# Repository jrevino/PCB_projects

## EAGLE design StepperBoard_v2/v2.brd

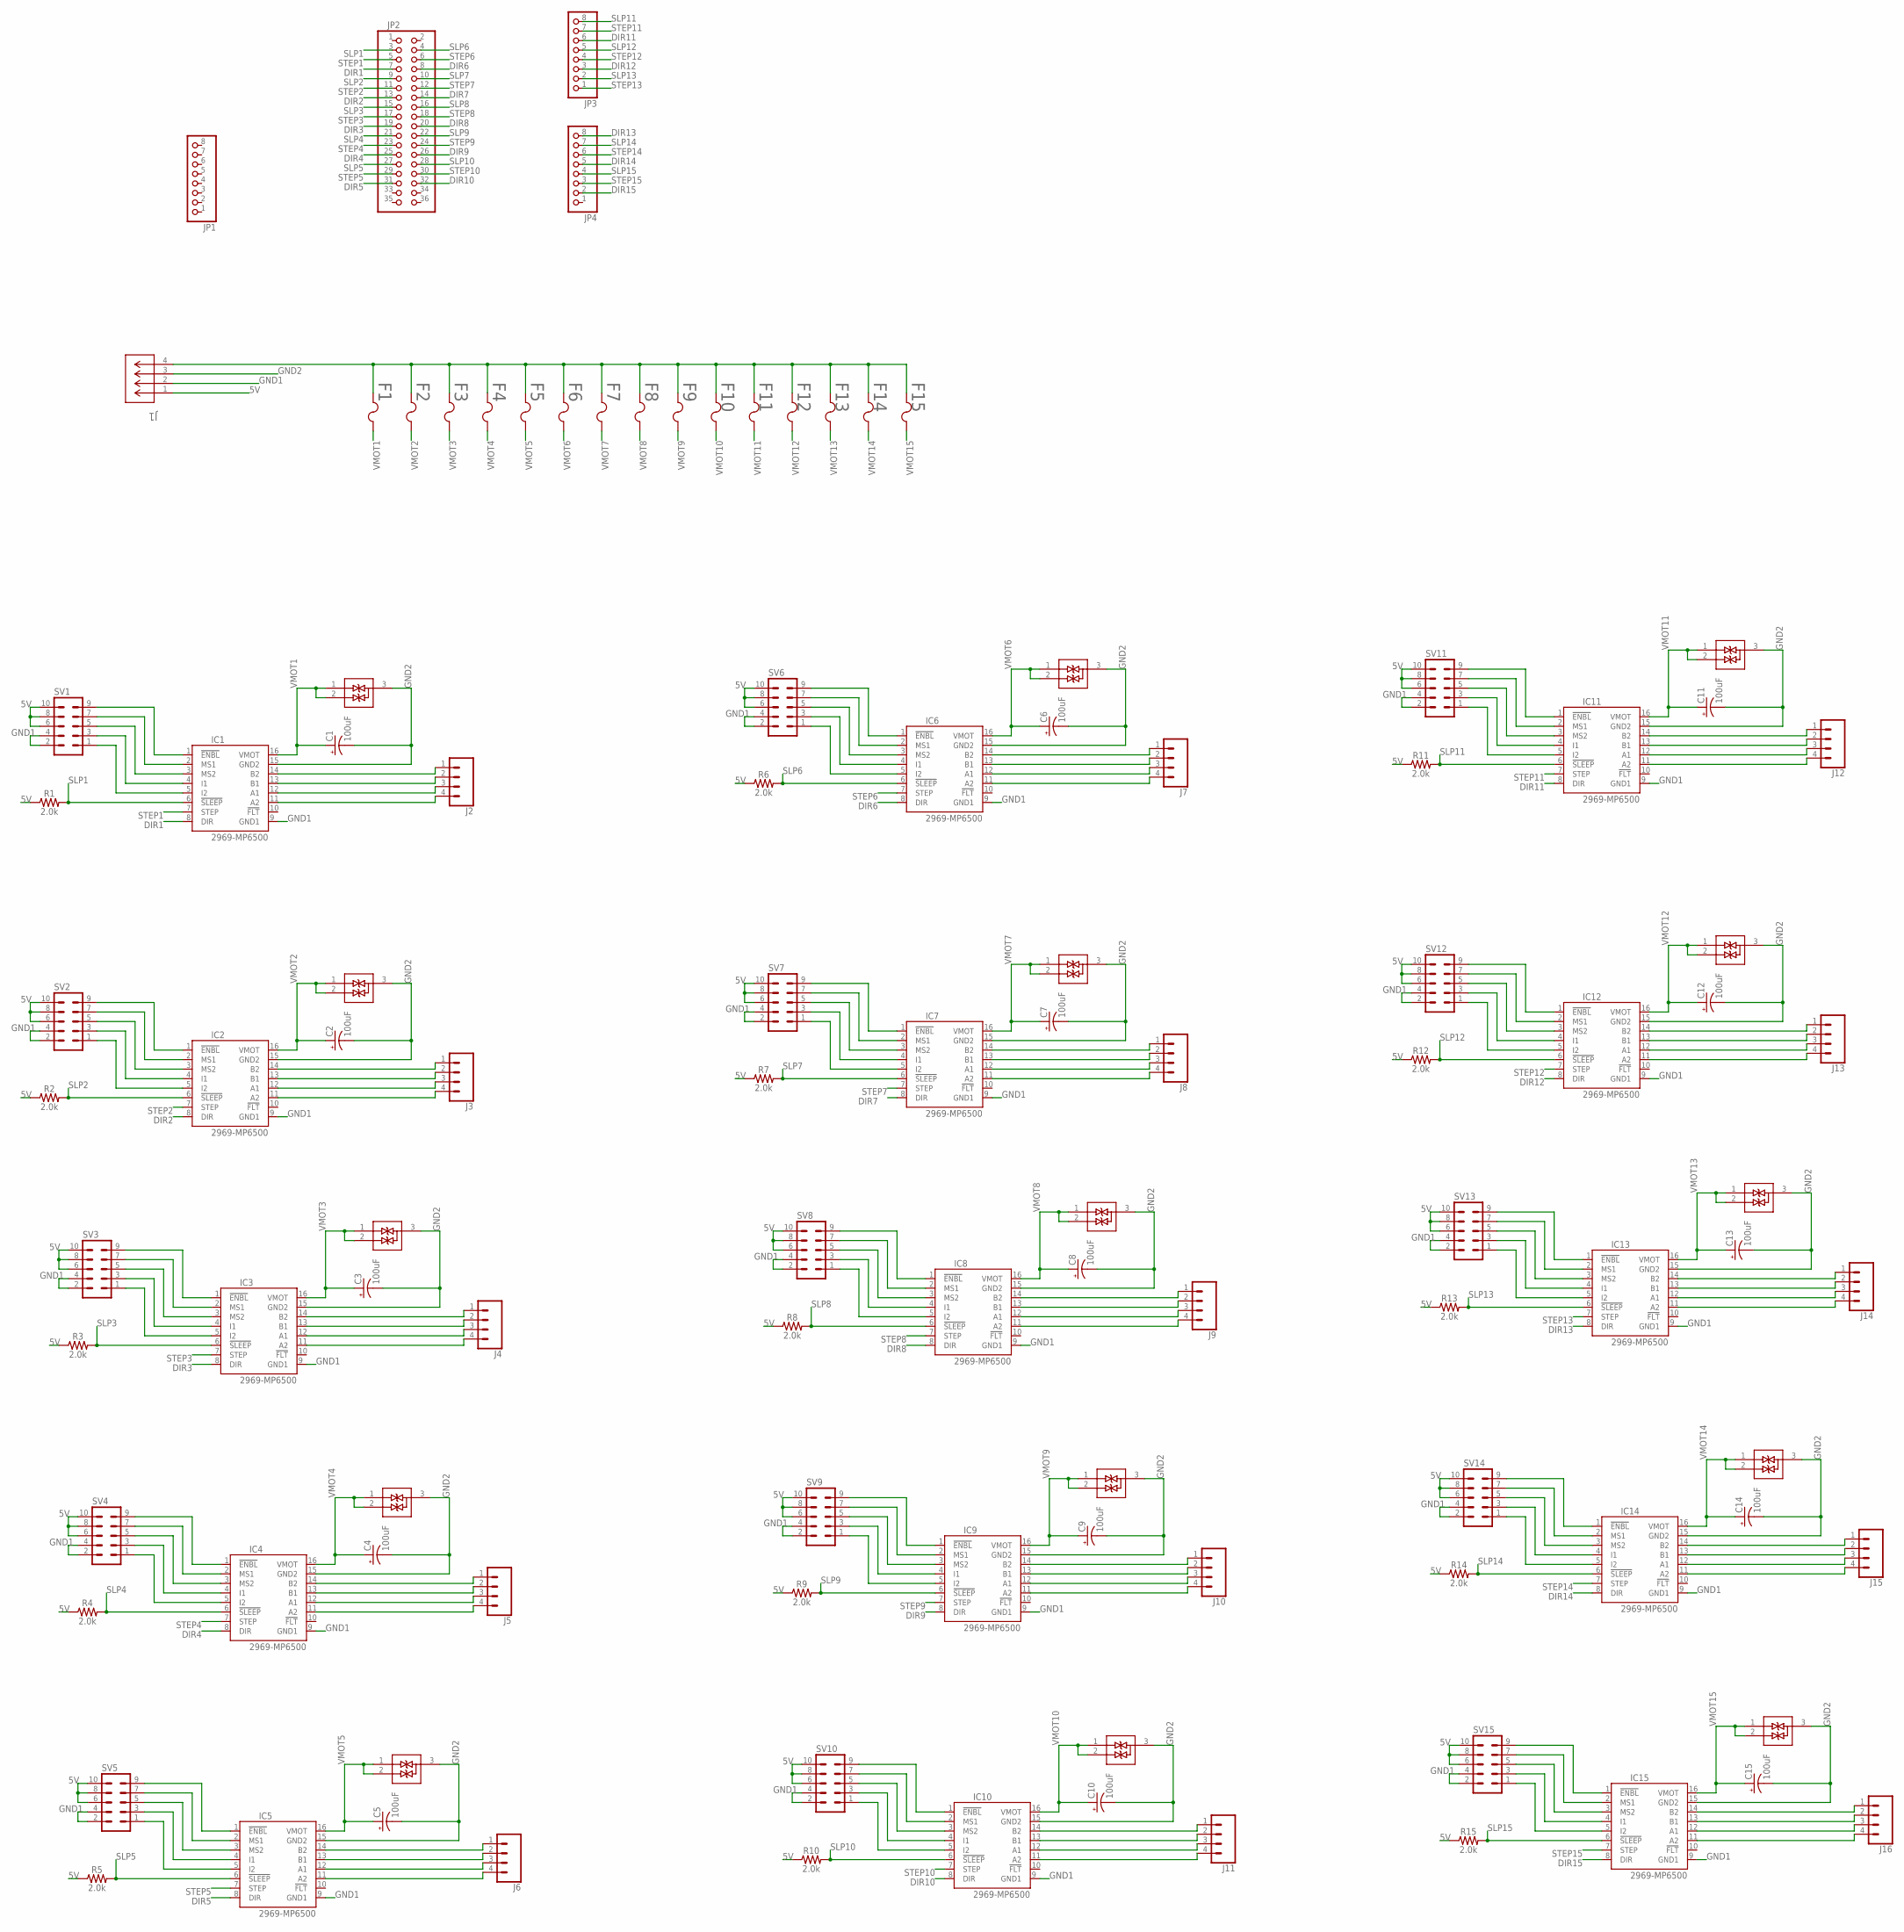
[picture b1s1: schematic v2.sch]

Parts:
C1, C2, C3, C4, C5, C6, C7, C8, C9, C10, C11, C12, C13, C14, C15: 100uF; 8X10.5
CR1, CR2, CR3, CR4, CR5, CR6, CR7, CR8, CR9, CR10, CR11, CR12, CR13, CR14, CR15: PESD2CAN24DBZRQ1; SOT-23_DBZ_TEX
F1, F2, F3, F4, F5, F6, F7, F8, F9, F10, F11, F12, F13, F14, F15: 0154003.DR; 0154SERIES_LTF
IC1, IC2, IC3, IC4, IC5, IC6, IC7, IC8, IC9, IC10, IC11, IC12, IC13, IC14, IC15: 2969-MP6500; MP6500
J1: 1888700; CONN_1888700_PXC
J2, J3, J4, J5, J6, J7, J8, J9, J10, J11, J12, J13, J14, J15, J16: CONN_04POLAR_LOCK; MOLEX-1X4_LOCK
JP1, JP3, JP4: PINHD-1X8; 1X08
JP2: PINHD-2X18; 2X18
R1, R2, R3, R4, R5, R6, R7, R8, R9, R10, R11, R12, R13, R14, R15: 2.0k; 0603
SV1, SV2, SV3, SV4, SV5, SV6, SV7, SV8, SV9, SV10, SV11, SV12, SV13, SV14, SV15: MA05-2

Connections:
5V: J1.1, R1.1, R2.1, R3.1, R4.1, R5.1, R6.1, R7.1, R8.1, R9.1, R10.1, R11.1, R12.1, R13.1, R14.1, R15.1, SV1.6, SV1.8, SV1.10, SV2.6, SV2.8, SV2.10, SV3.6, SV3.8, SV3.10, SV4.6, SV4.8, SV4.10, SV5.6, SV5.8, SV5.10, SV6.6, SV6.8, SV6.10, SV7.6, SV7.8, SV7.10, SV8.6, SV8.8, SV8.10, SV9.6, SV9.8, SV9.10, SV10.6, SV10.8, SV10.10, SV11.6, SV11.8, SV11.10, SV12.6, SV12.8, SV12.10, SV13.6, SV13.8, SV13.10, SV14.6, SV14.8, SV14.10, SV15.6, SV15.8, SV15.10
DIR1: IC1.8 (DIR), JP2.7
DIR2: IC2.8 (DIR), JP2.13
DIR3: IC3.8 (DIR), JP2.19
DIR4: IC4.8 (DIR), JP2.25
DIR5: IC5.8 (DIR), JP2.31
DIR6: IC6.8 (DIR), JP2.8
DIR7: IC7.8 (DIR), JP2.14
DIR8: IC8.8 (DIR), JP2.20
DIR9: IC9.8 (DIR), JP2.26
DIR10: IC10.8 (DIR), JP2.32
DIR11: IC11.8 (DIR), JP3.6
DIR12: IC12.8 (DIR), JP3.3
DIR13: IC13.8 (DIR), JP4.8
DIR14: IC14.8 (DIR), JP4.5
DIR15: IC15.8 (DIR), JP4.2
GND1: IC1.9 (GND1), IC2.9 (GND1), IC3.9 (GND1), IC4.9 (GND1), IC5.9 (GND1), IC6.9 (GND1), IC7.9 (GND1), IC8.9 (GND1), IC9.9 (GND1), IC10.9 (GND1), IC11.9 (GND1), IC12.9 (GND1), IC13.9 (GND1), IC14.9 (GND1), IC15.9 (GND1), J1.2, SV1.2, SV1.4, SV2.2, SV2.4, SV3.2, SV3.4, SV4.2, SV4.4, SV5.2, SV5.4, SV6.2, SV6.4, SV7.2, SV7.4, SV8.2, SV8.4, SV9.2, SV9.4, SV10.2, SV10.4, SV11.2, SV11.4, SV12.2, SV12.4, SV13.2, SV13.4, SV14.2, SV14.4, SV15.2, SV15.4
GND2: C1.-, C2.-, C3.-, C4.-, C5.-, C6.-, C7.-, C8.-, C9.-, C10.-, C11.-, C12.-, C13.-, C14.-, C15.-, CR1.3, CR2.3, CR3.3, CR4.3, CR5.3, CR6.3, CR7.3, CR8.3, CR9.3, CR10.3, CR11.3, CR12.3, CR13.3, CR14.3, CR15.3, IC1.15 (GND2), IC2.15 (GND2), IC3.15 (GND2), IC4.15 (GND2), IC5.15 (GND2), IC6.15 (GND2), IC7.15 (GND2), IC8.15 (GND2), IC9.15 (GND2), IC10.15 (GND2), IC11.15 (GND2), IC12.15 (GND2), IC13.15 (GND2), IC14.15 (GND2), IC15.15 (GND2), J1.3
unnamed: IC1.14 (B2), J2.1
unnamed: IC1.13 (B1), J2.2
unnamed: IC1.12 (A1), J2.3
unnamed: IC1.11 (A2), J2.4
unnamed: IC1.5 (I2), SV1.1
unnamed: IC1.4 (I1), SV1.3
unnamed: IC1.3 (MS2), SV1.5
unnamed: IC1.2 (MS1), SV1.7
unnamed: IC1.1 (!ENBL), SV1.9
unnamed: F1.1, F2.1, F3.1, F4.1, F5.1, F6.1, F7.1, F8.1, F9.1, F10.1, F11.1, F12.1, F13.1, F14.1, F15.1, J1.4
unnamed: IC2.5 (I2), SV2.1
unnamed: IC3.5 (I2), SV3.1
unnamed: IC3.4 (I1), SV3.3
unnamed: IC3.3 (MS2), SV3.5
unnamed: IC3.2 (MS1), SV3.7
unnamed: IC3.1 (!ENBL), SV3.9
unnamed: IC3.14 (B2), J4.1
unnamed: IC3.13 (B1), J4.2
unnamed: IC3.12 (A1), J4.3
unnamed: IC3.11 (A2), J4.4
unnamed: IC4.5 (I2), SV4.1
unnamed: IC4.4 (I1), SV4.3
unnamed: IC4.3 (MS2), SV4.5
unnamed: IC4.2 (MS1), SV4.7
unnamed: IC4.1 (!ENBL), SV4.9
unnamed: IC2.4 (I1), SV2.3
unnamed: IC2.3 (MS2), SV2.5
unnamed: IC2.2 (MS1), SV2.7
unnamed: IC2.1 (!ENBL), SV2.9
unnamed: IC2.14 (B2), J3.1
unnamed: IC2.13 (B1), J3.2
unnamed: IC2.12 (A1), J3.3
unnamed: IC2.11 (A2), J3.4
unnamed: IC4.14 (B2), J5.1
unnamed: IC4.13 (B1), J5.2
unnamed: IC4.12 (A1), J5.3
unnamed: IC4.11 (A2), J5.4
unnamed: IC6.5 (I2), SV6.1
unnamed: IC6.4 (I1), SV6.3
unnamed: IC6.3 (MS2), SV6.5
unnamed: IC6.2 (MS1), SV6.7
unnamed: IC6.1 (!ENBL), SV6.9
unnamed: IC6.14 (B2), J7.1
unnamed: IC6.13 (B1), J7.2
unnamed: IC6.12 (A1), J7.3
unnamed: IC6.11 (A2), J7.4
unnamed: IC5.5 (I2), SV5.1
unnamed: IC5.4 (I1), SV5.3
unnamed: IC5.3 (MS2), SV5.5
unnamed: IC5.2 (MS1), SV5.7
unnamed: IC5.1 (!ENBL), SV5.9
unnamed: IC5.14 (B2), J6.1
unnamed: IC5.13 (B1), J6.2
unnamed: IC5.12 (A1), J6.3
unnamed: IC5.11 (A2), J6.4
unnamed: IC7.5 (I2), SV7.1
unnamed: IC7.4 (I1), SV7.3
unnamed: IC7.3 (MS2), SV7.5
unnamed: IC7.2 (MS1), SV7.7
unnamed: IC7.1 (!ENBL), SV7.9
unnamed: IC7.14 (B2), J8.1
unnamed: IC7.13 (B1), J8.2
unnamed: IC7.12 (A1), J8.3
unnamed: IC7.11 (A2), J8.4
unnamed: IC8.5 (I2), SV8.1
unnamed: IC8.4 (I1), SV8.3
unnamed: IC8.3 (MS2), SV8.5
unnamed: IC8.2 (MS1), SV8.7
unnamed: IC8.1 (!ENBL), SV8.9
unnamed: IC8.14 (B2), J9.1
unnamed: IC8.13 (B1), J9.2
unnamed: IC8.12 (A1), J9.3
unnamed: IC8.11 (A2), J9.4
unnamed: IC9.5 (I2), SV9.1
unnamed: IC9.4 (I1), SV9.3
unnamed: IC9.3 (MS2), SV9.5
unnamed: IC9.2 (MS1), SV9.7
unnamed: IC9.1 (!ENBL), SV9.9
unnamed: IC9.14 (B2), J10.1
unnamed: IC9.13 (B1), J10.2
unnamed: IC9.12 (A1), J10.3
unnamed: IC9.11 (A2), J10.4
unnamed: IC10.5 (I2), SV10.1
unnamed: IC10.4 (I1), SV10.3
unnamed: IC10.3 (MS2), SV10.5
unnamed: IC10.2 (MS1), SV10.7
unnamed: IC10.1 (!ENBL), SV10.9
unnamed: IC10.14 (B2), J11.1
unnamed: IC10.13 (B1), J11.2
unnamed: IC10.12 (A1), J11.3
unnamed: IC10.11 (A2), J11.4
unnamed: IC11.5 (I2), SV11.1
unnamed: IC11.4 (I1), SV11.3
unnamed: IC11.3 (MS2), SV11.5
unnamed: IC11.2 (MS1), SV11.7
unnamed: IC11.1 (!ENBL), SV11.9
unnamed: IC11.14 (B2), J12.1
unnamed: IC11.13 (B1), J12.2
unnamed: IC11.12 (A1), J12.3
unnamed: IC11.11 (A2), J12.4
unnamed: IC12.5 (I2), SV12.1
unnamed: IC12.4 (I1), SV12.3
unnamed: IC12.3 (MS2), SV12.5
unnamed: IC12.2 (MS1), SV12.7
unnamed: IC12.1 (!ENBL), SV12.9
unnamed: IC12.14 (B2), J13.1
unnamed: IC12.13 (B1), J13.2
unnamed: IC12.12 (A1), J13.3
unnamed: IC12.11 (A2), J13.4
unnamed: IC13.5 (I2), SV13.1
unnamed: IC13.4 (I1), SV13.3
unnamed: IC13.3 (MS2), SV13.5
unnamed: IC13.2 (MS1), SV13.7
unnamed: IC13.1 (!ENBL), SV13.9
unnamed: IC13.14 (B2), J14.1
unnamed: IC13.13 (B1), J14.2
unnamed: IC13.12 (A1), J14.3
unnamed: IC13.11 (A2), J14.4
unnamed: IC14.5 (I2), SV14.1
unnamed: IC14.4 (I1), SV14.3
unnamed: IC14.3 (MS2), SV14.5
unnamed: IC14.2 (MS1), SV14.7
unnamed: IC14.1 (!ENBL), SV14.9
unnamed: IC14.14 (B2), J15.1
unnamed: IC14.13 (B1), J15.2
unnamed: IC14.12 (A1), J15.3
unnamed: IC14.11 (A2), J15.4
unnamed: IC15.5 (I2), SV15.1
unnamed: IC15.4 (I1), SV15.3
unnamed: IC15.3 (MS2), SV15.5
unnamed: IC15.2 (MS1), SV15.7
unnamed: IC15.1 (!ENBL), SV15.9
unnamed: IC15.14 (B2), J16.1
unnamed: IC15.13 (B1), J16.2
unnamed: IC15.12 (A1), J16.3
unnamed: IC15.11 (A2), J16.4
SLP1: IC1.6 (!SLEEP), JP2.3, R1.2
SLP2: IC2.6 (!SLEEP), JP2.9, R2.2
SLP3: IC3.6 (!SLEEP), JP2.15, R3.2
SLP4: IC4.6 (!SLEEP), JP2.21, R4.2
SLP5: IC5.6 (!SLEEP), JP2.27, R5.2
SLP6: IC6.6 (!SLEEP), JP2.4, R6.2
SLP7: IC7.6 (!SLEEP), JP2.10, R7.2
SLP8: IC8.6 (!SLEEP), JP2.16, R8.2
SLP9: IC9.6 (!SLEEP), JP2.22, R9.2
SLP10: IC10.6 (!SLEEP), JP2.28, R10.2
SLP11: IC11.6 (!SLEEP), JP3.8, R11.2
SLP12: IC12.6 (!SLEEP), JP3.5, R12.2
SLP13: IC13.6 (!SLEEP), JP3.2, R13.2
SLP14: IC14.6 (!SLEEP), JP4.7, R14.2
SLP15: IC15.6 (!SLEEP), JP4.4, R15.2
STEP1: IC1.7 (STEP), JP2.5
STEP2: IC2.7 (STEP), JP2.11
STEP3: IC3.7 (STEP), JP2.17
STEP4: IC4.7 (STEP), JP2.23
STEP5: IC5.7 (STEP), JP2.29
STEP6: IC6.7 (STEP), JP2.6
STEP7: IC7.7 (STEP), JP2.12
STEP8: IC8.7 (STEP), JP2.18
STEP9: IC9.7 (STEP), JP2.24
STEP10: IC10.7 (STEP), JP2.30
STEP11: IC11.7 (STEP), JP3.7
STEP12: IC12.7 (STEP), JP3.4
STEP13: IC13.7 (STEP), JP3.1
STEP14: IC14.7 (STEP), JP4.6
STEP15: IC15.7 (STEP), JP4.3
VMOT1: C1.+, CR1.1, CR1.2, F1.2, IC1.16 (VMOT)
VMOT2: C2.+, CR2.1, CR2.2, F2.2, IC2.16 (VMOT)
VMOT3: C3.+, CR3.1, CR3.2, F3.2, IC3.16 (VMOT)
VMOT4: C4.+, CR4.1, CR4.2, F4.2, IC4.16 (VMOT)
VMOT5: C5.+, CR5.1, CR5.2, F5.2, IC5.16 (VMOT)
VMOT6: C6.+, CR6.1, CR6.2, F6.2, IC6.16 (VMOT)
VMOT7: C7.+, CR7.1, CR7.2, F7.2, IC7.16 (VMOT)
VMOT8: C8.+, CR8.1, CR8.2, F8.2, IC8.16 (VMOT)
VMOT9: C9.+, CR9.1, CR9.2, F9.2, IC9.16 (VMOT)
VMOT10: C10.+, CR10.1, CR10.2, F10.2, IC10.16 (VMOT)
VMOT11: C11.+, CR11.1, CR11.2, F11.2, IC11.16 (VMOT)
VMOT12: C12.+, CR12.1, CR12.2, F12.2, IC12.16 (VMOT)
VMOT13: C13.+, CR13.1, CR13.2, F13.2, IC13.16 (VMOT)
VMOT14: C14.+, CR14.1, CR14.2, F14.2, IC14.16 (VMOT)
VMOT15: C15.+, CR15.1, CR15.2, F15.2, IC15.16 (VMOT)

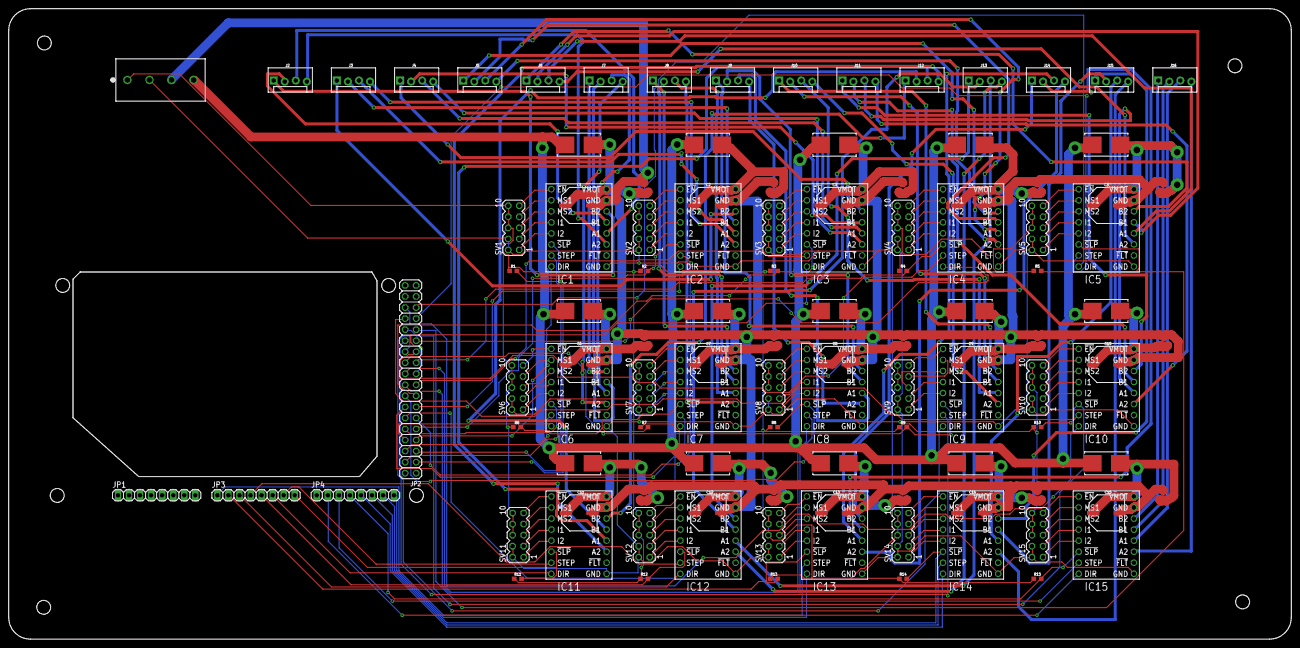
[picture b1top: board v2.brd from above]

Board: 2 copper layers, 295.0 x 145.0 mm, 110 parts (0 on the bottom side), 199 nets.

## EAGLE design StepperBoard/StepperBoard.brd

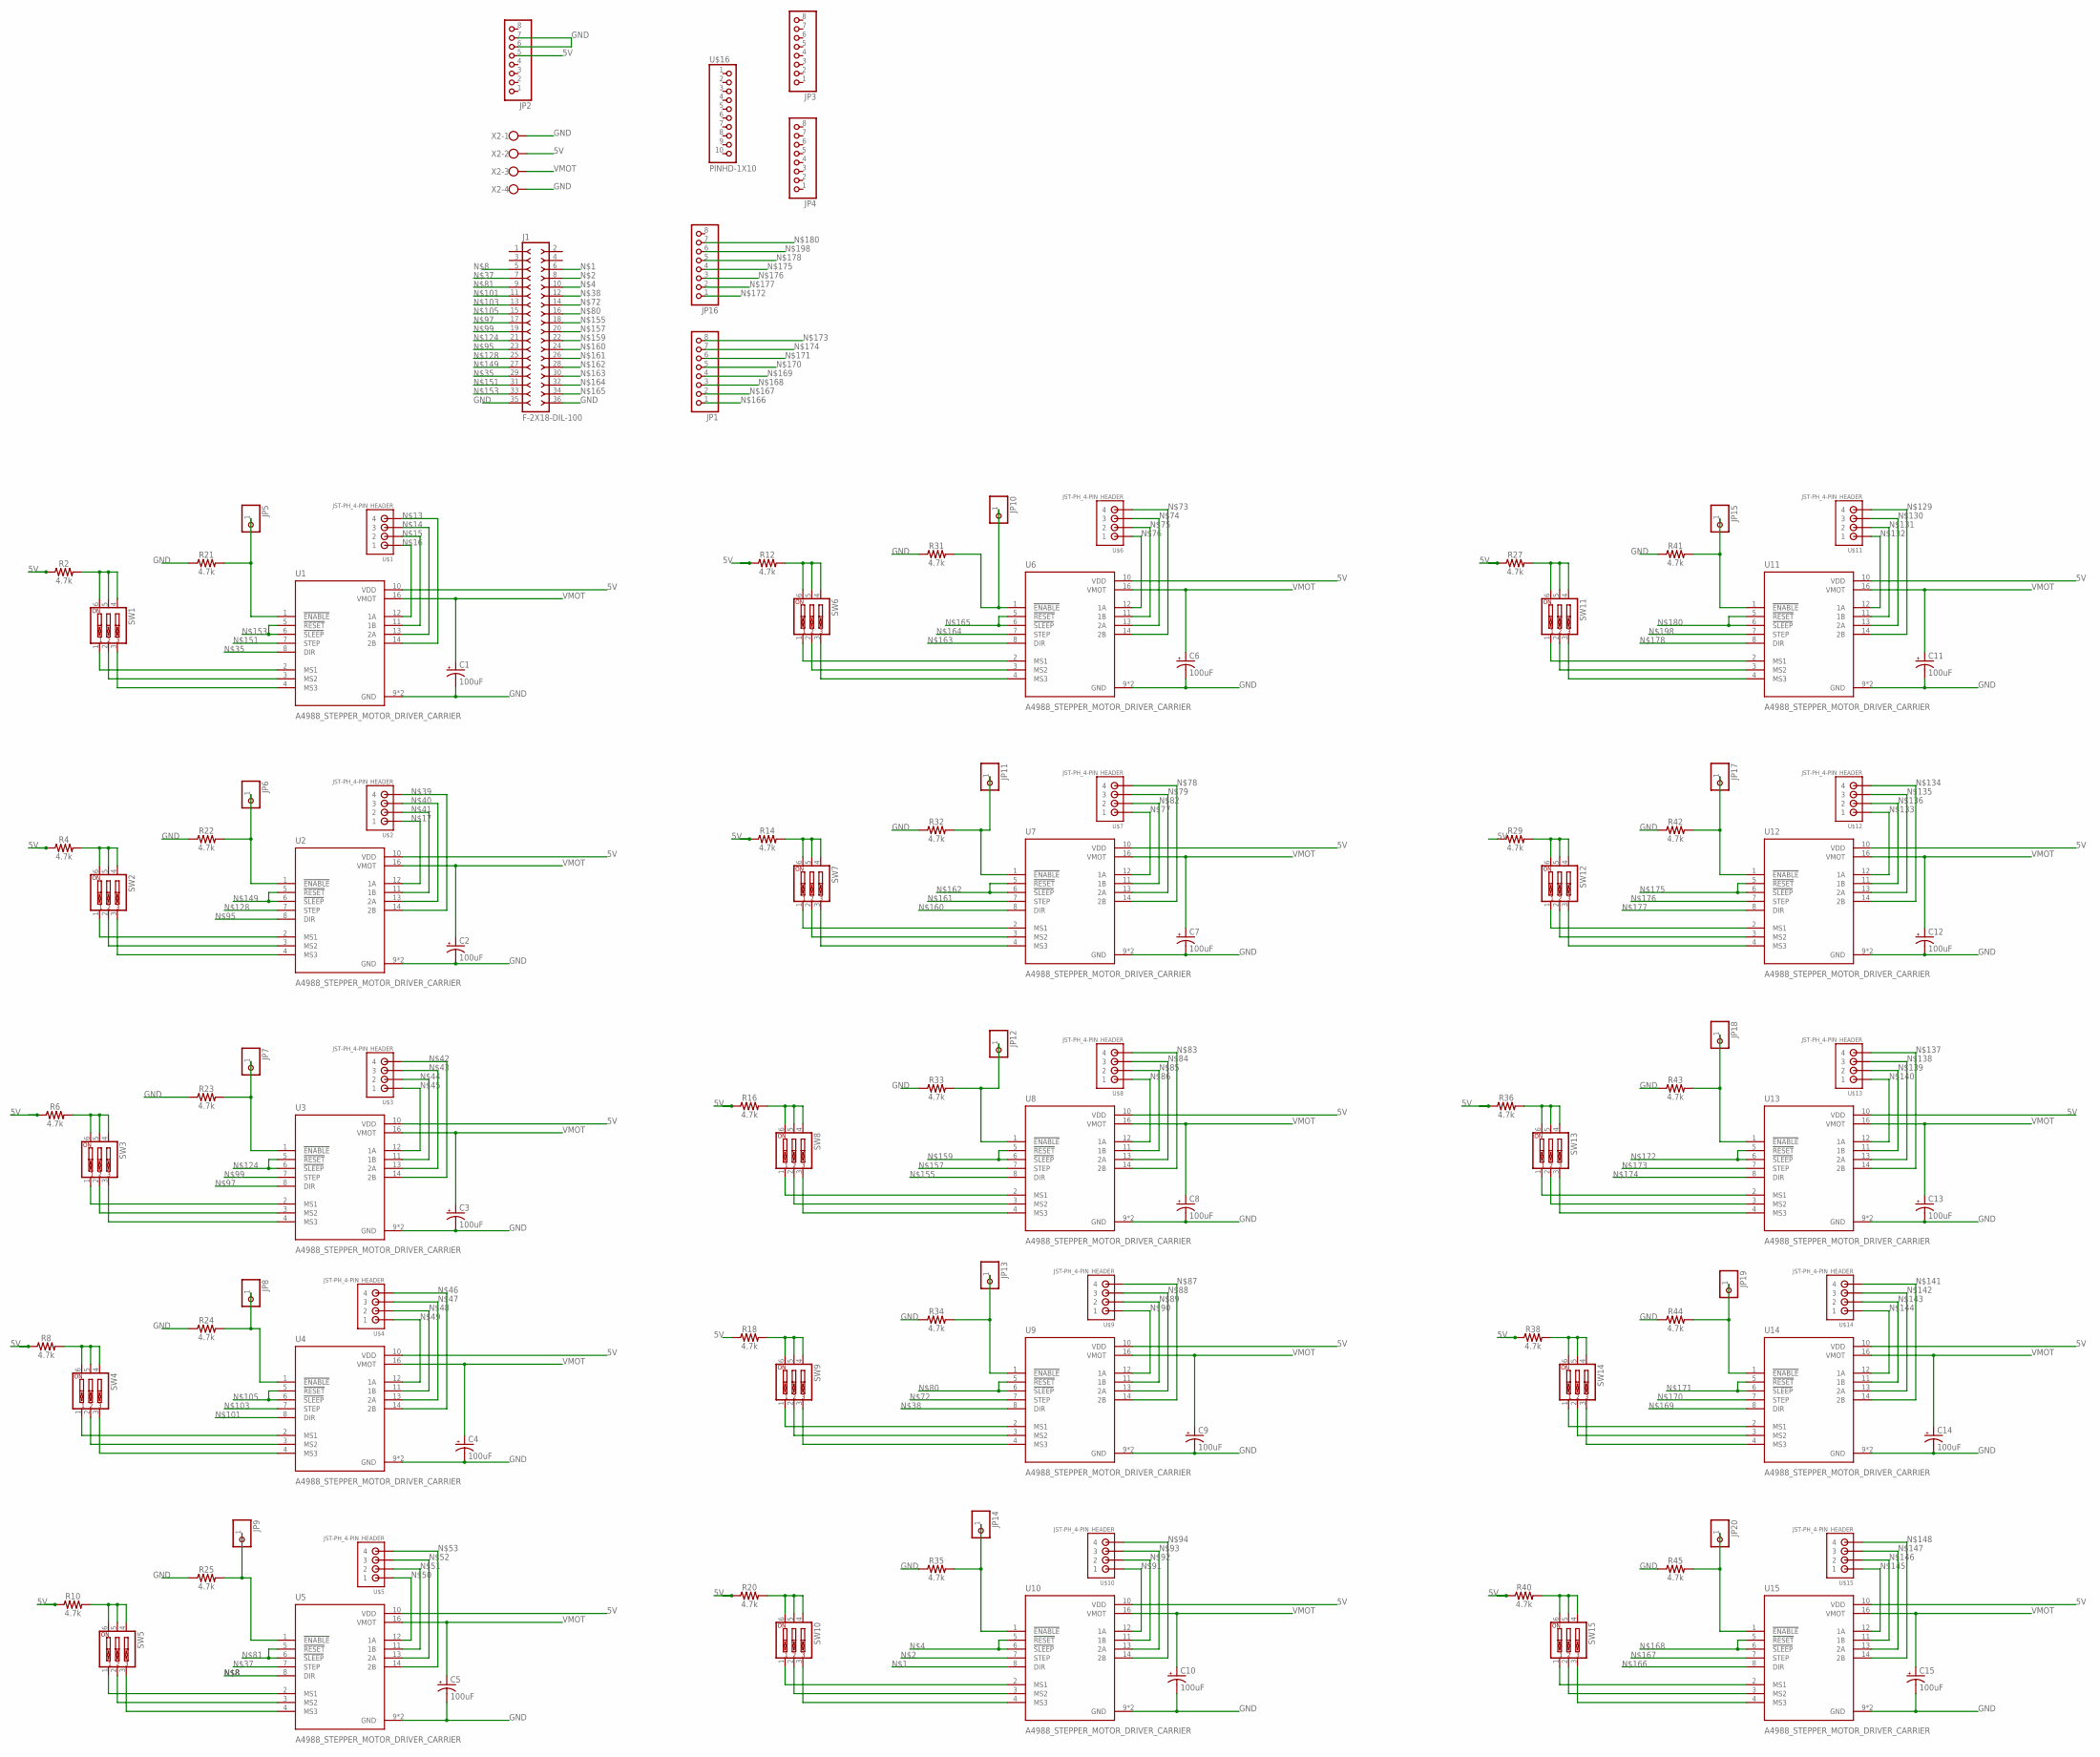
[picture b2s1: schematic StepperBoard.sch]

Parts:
C1, C2, C3, C4, C5, C6, C7, C8, C9, C10, C11, C12, C13, C14, C15: 100uF; CPOL-RADIAL-2.5MM-6.5MM
J1: F-2X18-DIL-100; DIL-100-2X18
JP1, JP2, JP3, JP4, JP16: PINHD-1X8; 1X08
JP5, JP6, JP7, JP8, JP9, JP10, JP11, JP12, JP13, JP14, JP15, JP17, JP18, JP19, JP20: PINHD-1X1; 1X01
R2, R4, R6, R8, R10, R12, R14, R16, R18, R20, R21, R22, R23, R24, R25, R27, R29, R31, R32, R33, R34, R35, R36, R38, R40, R41, R42, R43, R44, R45: 4.7k; 0603
SW1, SW2, SW3, SW4, SW5, SW6, SW7, SW8, SW9, SW10, SW11, SW12, SW13, SW14, SW15: SW_DIP-3; EDG-03
U1, U2, U3, U4, U5, U6, U7, U8, U9, U10, U11, U12, U13, U14, U15: A4988_STEPPER_MOTOR_DRIVER_CARRIER; MODULE_A4988_STEPPER_MOTOR_DRIVER_CARRIER
U$1, U$2, U$3, U$4, U$5, U$6, U$7, U$8, U$9, U$10, U$11, U$12, U$13, U$14, U$15: JST-PH_4-PIN_HEADER; JST_B4B-PH_HEADER
U$16: PINHD-1X10; 1X10-BIG
X2: W237-4

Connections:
5V: JP2.5, R2.1, R4.1, R6.1, R8.1, R10.1, R12.1, R14.1, R16.1, R18.1, R20.1, R27.1, R29.1, R36.1, R38.1, R40.1, U1.10 (VDD), U2.10 (VDD), U3.10 (VDD), U4.10 (VDD), U5.10 (VDD), U6.10 (VDD), U7.10 (VDD), U8.10 (VDD), U9.10 (VDD), U10.10 (VDD), U11.10 (VDD), U12.10 (VDD), U13.10 (VDD), U14.10 (VDD), U15.10 (VDD), X2.2
GND: C1.2 (-), C2.2 (-), C3.2 (-), C4.2 (-), C5.2 (-), C6.2 (-), C7.2 (-), C8.2 (-), C9.2 (-), C10.2 (-), C11.2 (-), C12.2 (-), C13.2 (-), C14.2 (-), C15.2 (-), J1.35, J1.36, JP2.6, JP2.7, R21.1, R22.1, R23.1, R24.1, R25.1, R31.1, R32.1, R33.1, R34.1, R35.1, R41.1, R42.1, R43.1, R44.1, R45.1, U1.9 (GND), U1.15 (GND), U2.9 (GND), U2.15 (GND), U3.9 (GND), U3.15 (GND), U4.9 (GND), U4.15 (GND), U5.9 (GND), U5.15 (GND), U6.9 (GND), U6.15 (GND), U7.9 (GND), U7.15 (GND), U8.9 (GND), U8.15 (GND), U9.9 (GND), U9.15 (GND), U10.9 (GND), U10.15 (GND), U11.9 (GND), U11.15 (GND), U12.9 (GND), U12.15 (GND), U13.9 (GND), U13.15 (GND), U14.9 (GND), U14.15 (GND), U15.9 (GND), U15.15 (GND), X2.1, X2.4
unnamed: J1.6, U10.8 (DIR)
unnamed: J1.8, U10.7 (STEP)
unnamed: JP5.1, R21.2, U1.1 (!ENABLE)
unnamed: J1.10, U10.5 (!RESET), U10.6 (!SLEEP)
unnamed: R14.2, SW7.4, SW7.5, SW7.6
unnamed: SW7.3, U7.4 (MS3)
unnamed: SW7.2, U7.3 (MS2)
unnamed: J1.5, U5.8 (DIR)
unnamed: R4.2, SW2.4, SW2.5, SW2.6
unnamed: SW2.3, U2.4 (MS3)
unnamed: SW2.2, U2.3 (MS2)
unnamed: SW2.1, U2.2 (MS1)
unnamed: U1.14 (2B), U$1.P4 (4)
unnamed: U1.13 (2A), U$1.P3 (3)
unnamed: U1.11 (1B), U$1.P2 (2)
unnamed: U1.12 (1A), U$1.P1 (1)
unnamed: U2.12 (1A), U$2.P1 (1)
unnamed: SW1.3, U1.4 (MS3)
unnamed: SW1.2, U1.3 (MS2)
unnamed: SW1.1, U1.2 (MS1)
unnamed: R2.2, SW1.4, SW1.5, SW1.6
unnamed: R6.2, SW3.4, SW3.5, SW3.6
unnamed: SW3.3, U3.4 (MS3)
unnamed: SW3.2, U3.3 (MS2)
unnamed: SW3.1, U3.2 (MS1)
unnamed: R8.2, SW4.4, SW4.5, SW4.6
unnamed: SW4.3, U4.4 (MS3)
unnamed: SW4.2, U4.3 (MS2)
unnamed: SW4.1, U4.2 (MS1)
unnamed: R10.2, SW5.4, SW5.5, SW5.6
unnamed: SW5.3, U5.4 (MS3)
unnamed: SW5.2, U5.3 (MS2)
unnamed: SW5.1, U5.2 (MS1)
unnamed: JP6.1, R22.2, U2.1 (!ENABLE)
unnamed: J1.29, U1.8 (DIR)
unnamed: JP7.1, R23.2, U3.1 (!ENABLE)
unnamed: J1.7, U5.7 (STEP)
unnamed: J1.12, U9.8 (DIR)
unnamed: U2.14 (2B), U$2.P4 (4)
unnamed: U2.13 (2A), U$2.P3 (3)
unnamed: U2.11 (1B), U$2.P2 (2)
unnamed: U3.14 (2B), U$3.P4 (4)
unnamed: U3.13 (2A), U$3.P3 (3)
unnamed: U3.11 (1B), U$3.P2 (2)
unnamed: U3.12 (1A), U$3.P1 (1)
unnamed: U4.14 (2B), U$4.P4 (4)
unnamed: U4.13 (2A), U$4.P3 (3)
unnamed: U4.11 (1B), U$4.P2 (2)
unnamed: U4.12 (1A), U$4.P1 (1)
unnamed: U5.12 (1A), U$5.P1 (1)
unnamed: U5.11 (1B), U$5.P2 (2)
unnamed: U5.13 (2A), U$5.P3 (3)
unnamed: U5.14 (2B), U$5.P4 (4)
unnamed: JP8.1, R24.2, U4.1 (!ENABLE)
unnamed: SW7.1, U7.2 (MS1)
unnamed: R16.2, SW8.4, SW8.5, SW8.6
unnamed: SW8.3, U8.4 (MS3)
unnamed: SW8.2, U8.3 (MS2)
unnamed: SW8.1, U8.2 (MS1)
unnamed: R18.2, SW9.4, SW9.5, SW9.6
unnamed: SW9.3, U9.4 (MS3)
unnamed: SW9.2, U9.3 (MS2)
unnamed: SW9.1, U9.2 (MS1)
unnamed: R20.2, SW10.4, SW10.5, SW10.6
unnamed: SW10.3, U10.4 (MS3)
unnamed: SW10.2, U10.3 (MS2)
unnamed: SW10.1, U10.2 (MS1)
unnamed: R12.2, SW6.4, SW6.5, SW6.6
unnamed: SW6.3, U6.4 (MS3)
unnamed: SW6.2, U6.3 (MS2)
unnamed: SW6.1, U6.2 (MS1)
unnamed: J1.14, U9.7 (STEP)
unnamed: U6.14 (2B), U$6.P4 (4)
unnamed: U6.13 (2A), U$6.P3 (3)
unnamed: U6.11 (1B), U$6.P2 (2)
unnamed: U6.12 (1A), U$6.P1 (1)
unnamed: U7.12 (1A), U$7.P1 (1)
unnamed: U7.14 (2B), U$7.P4 (4)
unnamed: U7.13 (2A), U$7.P3 (3)
unnamed: J1.16, U9.5 (!RESET), U9.6 (!SLEEP)
unnamed: J1.9, U5.5 (!RESET), U5.6 (!SLEEP)
unnamed: U7.11 (1B), U$7.P2 (2)
unnamed: U8.14 (2B), U$8.P4 (4)
unnamed: U8.13 (2A), U$8.P3 (3)
unnamed: U8.11 (1B), U$8.P2 (2)
unnamed: U8.12 (1A), U$8.P1 (1)
unnamed: U9.14 (2B), U$9.P4 (4)
unnamed: U9.13 (2A), U$9.P3 (3)
unnamed: U9.11 (1B), U$9.P2 (2)
unnamed: U9.12 (1A), U$9.P1 (1)
unnamed: U10.12 (1A), U$10.P1 (1)
unnamed: U10.11 (1B), U$10.P2 (2)
unnamed: U10.13 (2A), U$10.P3 (3)
unnamed: U10.14 (2B), U$10.P4 (4)
unnamed: J1.23, U2.8 (DIR)
unnamed: JP10.1, R31.2, U6.1 (!ENABLE)
unnamed: J1.17, U3.8 (DIR)
unnamed: JP11.1, R32.2, U7.1 (!ENABLE)
unnamed: J1.19, U3.7 (STEP)
unnamed: JP12.1, R33.2, U8.1 (!ENABLE)
unnamed: J1.11, U4.8 (DIR)
unnamed: JP13.1, R34.2, U9.1 (!ENABLE)
unnamed: J1.13, U4.7 (STEP)
unnamed: JP14.1, R35.2, U10.1 (!ENABLE)
unnamed: J1.15, U4.5 (!RESET), U4.6 (!SLEEP)
unnamed: R29.2, SW12.4, SW12.5, SW12.6
unnamed: SW12.3, U12.4 (MS3)
unnamed: SW12.2, U12.3 (MS2)
unnamed: SW12.1, U12.2 (MS1)
unnamed: R36.2, SW13.4, SW13.5, SW13.6
unnamed: SW13.3, U13.4 (MS3)
unnamed: SW13.2, U13.3 (MS2)
unnamed: SW13.1, U13.2 (MS1)
unnamed: R38.2, SW14.4, SW14.5, SW14.6
unnamed: SW14.3, U14.4 (MS3)
unnamed: SW14.2, U14.3 (MS2)
unnamed: SW14.1, U14.2 (MS1)
unnamed: R40.2, SW15.4, SW15.5, SW15.6
unnamed: SW15.3, U15.4 (MS3)
unnamed: SW15.2, U15.3 (MS2)
unnamed: SW15.1, U15.2 (MS1)
unnamed: R27.2, SW11.4, SW11.5, SW11.6
unnamed: JP9.1, R25.2, U5.1 (!ENABLE)
unnamed: J1.21, U3.5 (!RESET), U3.6 (!SLEEP)
unnamed: SW11.3, U11.4 (MS3)
unnamed: SW11.2, U11.3 (MS2)
unnamed: SW11.1, U11.2 (MS1)
unnamed: J1.25, U2.7 (STEP)
unnamed: U11.14 (2B), U$11.P4 (4)
unnamed: U11.13 (2A), U$11.P3 (3)
unnamed: U11.11 (1B), U$11.P2 (2)
unnamed: U11.12 (1A), U$11.P1 (1)
unnamed: U12.12 (1A), U$12.P1 (1)
unnamed: U12.14 (2B), U$12.P4 (4)
unnamed: U12.13 (2A), U$12.P3 (3)
unnamed: U12.11 (1B), U$12.P2 (2)
unnamed: U13.14 (2B), U$13.P4 (4)
unnamed: U13.13 (2A), U$13.P3 (3)
unnamed: U13.11 (1B), U$13.P2 (2)
unnamed: U13.12 (1A), U$13.P1 (1)
unnamed: U14.14 (2B), U$14.P4 (4)
unnamed: U14.13 (2A), U$14.P3 (3)
unnamed: U14.11 (1B), U$14.P2 (2)
unnamed: U14.12 (1A), U$14.P1 (1)
unnamed: U15.12 (1A), U$15.P1 (1)
unnamed: U15.11 (1B), U$15.P2 (2)
unnamed: U15.13 (2A), U$15.P3 (3)
unnamed: U15.14 (2B), U$15.P4 (4)
unnamed: J1.27, U2.5 (!RESET), U2.6 (!SLEEP)
unnamed: JP15.1, R41.2, U11.1 (!ENABLE)
unnamed: J1.31, U1.7 (STEP)
unnamed: JP17.1, R42.2, U12.1 (!ENABLE)
unnamed: J1.33, U1.5 (!RESET), U1.6 (!SLEEP)
unnamed: JP18.1, R43.2, U13.1 (!ENABLE)
unnamed: J1.18, U8.8 (DIR)
unnamed: JP19.1, R44.2, U14.1 (!ENABLE)
unnamed: J1.20, U8.7 (STEP)
unnamed: JP20.1, R45.2, U15.1 (!ENABLE)
unnamed: J1.22, U8.5 (!RESET), U8.6 (!SLEEP)
unnamed: J1.24, U7.8 (DIR)
unnamed: J1.26, U7.7 (STEP)
unnamed: J1.28, U7.5 (!RESET), U7.6 (!SLEEP)
unnamed: J1.30, U6.8 (DIR)
unnamed: J1.32, U6.7 (STEP)
unnamed: J1.34, U6.5 (!RESET), U6.6 (!SLEEP)
unnamed: JP1.1, U15.8 (DIR)
unnamed: JP1.2, U15.7 (STEP)
unnamed: JP1.3, U15.5 (!RESET), U15.6 (!SLEEP)
unnamed: JP1.4, U14.8 (DIR)
unnamed: JP1.5, U14.7 (STEP)
unnamed: JP1.6, U14.5 (!RESET), U14.6 (!SLEEP)
unnamed: JP16.1, U13.5 (!RESET), U13.6 (!SLEEP)
unnamed: JP1.8, U13.7 (STEP)
unnamed: JP1.7, U13.8 (DIR)
unnamed: JP16.4, U12.5 (!RESET), U12.6 (!SLEEP)
unnamed: JP16.3, U12.7 (STEP)
unnamed: JP16.2, U12.8 (DIR)
unnamed: JP16.5, U11.8 (DIR)
unnamed: JP16.7, U11.5 (!RESET), U11.6 (!SLEEP)
unnamed: JP16.6, U11.7 (STEP)
VMOT: C1.1 (+), C2.1 (+), C3.1 (+), C4.1 (+), C5.1 (+), C6.1 (+), C7.1 (+), C8.1 (+), C9.1 (+), C10.1 (+), C11.1 (+), C12.1 (+), C13.1 (+), C14.1 (+), C15.1 (+), U1.16 (VMOT), U2.16 (VMOT), U3.16 (VMOT), U4.16 (VMOT), U5.16 (VMOT), U6.16 (VMOT), U7.16 (VMOT), U8.16 (VMOT), U9.16 (VMOT), U10.16 (VMOT), U11.16 (VMOT), U12.16 (VMOT), U13.16 (VMOT), U14.16 (VMOT), U15.16 (VMOT), X2.3

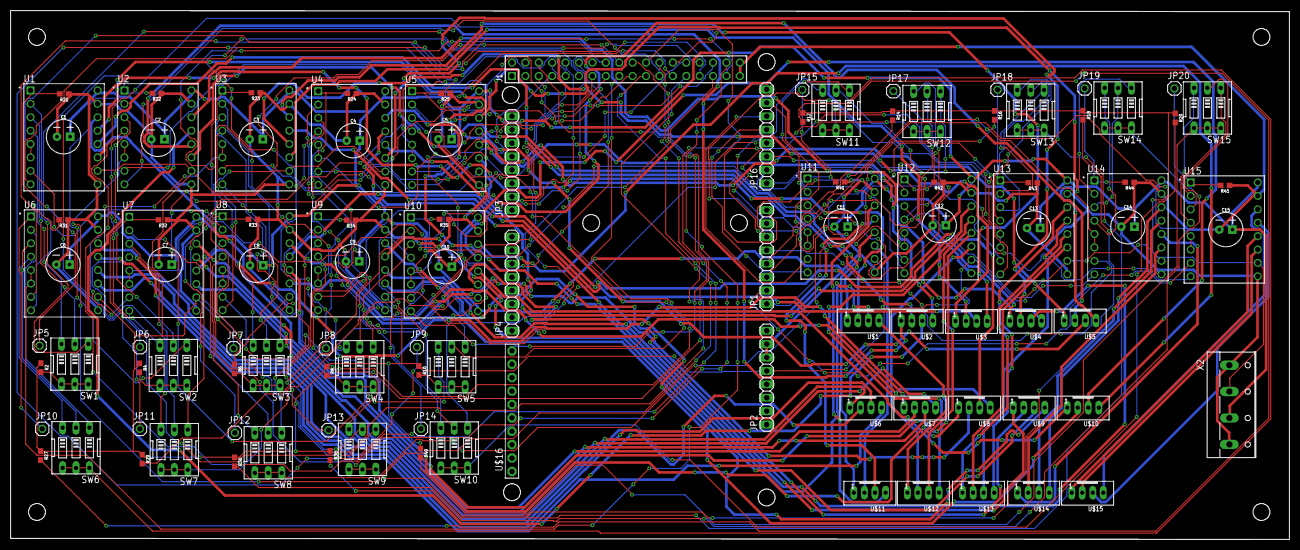
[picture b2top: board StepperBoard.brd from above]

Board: 2 copper layers, 242.3 x 100.2 mm, 113 parts (0 on the bottom side), 183 nets.

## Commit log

2023-03-14 Adding design files
2023-03-20 Add files via upload
    Board design updated
2023-03-20 Added finishing touches
2023-03-21 Updated trace widths
2023-03-22 Switched to net labels instead of long wires
2023-04-13 Updated PCB for MP6500 driver board
2023-04-15 Made recommended changes
2023-04-28 Design is ready for order

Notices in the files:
parts and their libraries:
SparkFun-Capacitors: Licensing: Creative Commons ShareAlike 4.0 International - https://creativecommons.org/licenses/by-sa/4.0
con-headers-jp: Copyright (C) 2008, Bob Starr
COPYRIGHT: Copyright (C) 2023 Ultra Librarian. All rights reserved.
